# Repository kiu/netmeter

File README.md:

# netmeter
*netmeter* is a trio of analog panel meters showing the up-/download speed of my AVM FRITZ!Box 7360 and ping roundtrip times.

Video: https://youtu.be/6VHqjQCAy3I

# Inspiration
*netmeter* is inspired by the 10 year old [megabitmeter](http://dk7sl.de/2010/11/11/megabitmeter/) and its - now defunct - commercial version [megabitmeter](http://megabitmeter.de).

# Tech Details
The [ESP32-DevKitC V4](https://www.espressif.com/en/products/devkits/esp32-devkitc) offers a powerful plug and play solution providing the core functionality of *netmeter*.
It connects to the network via wifi and polls the [UPnP](https://en.wikipedia.org/wiki/Universal_Plug_and_Play) interface of the FRITZ!Box obtaining the current transmitted and received bytes count of the WAN interface. In addition it runs a simple ping command to determine the roundtrip time. The results are transformed into PWM signals driving the meters.

The mechanical design features horizontal and vertical mounting of the panel meters. The included custom scales can be omitted to save costs. In that case a standard scale - e.g. 100A = 100 MBit/s - can be used.

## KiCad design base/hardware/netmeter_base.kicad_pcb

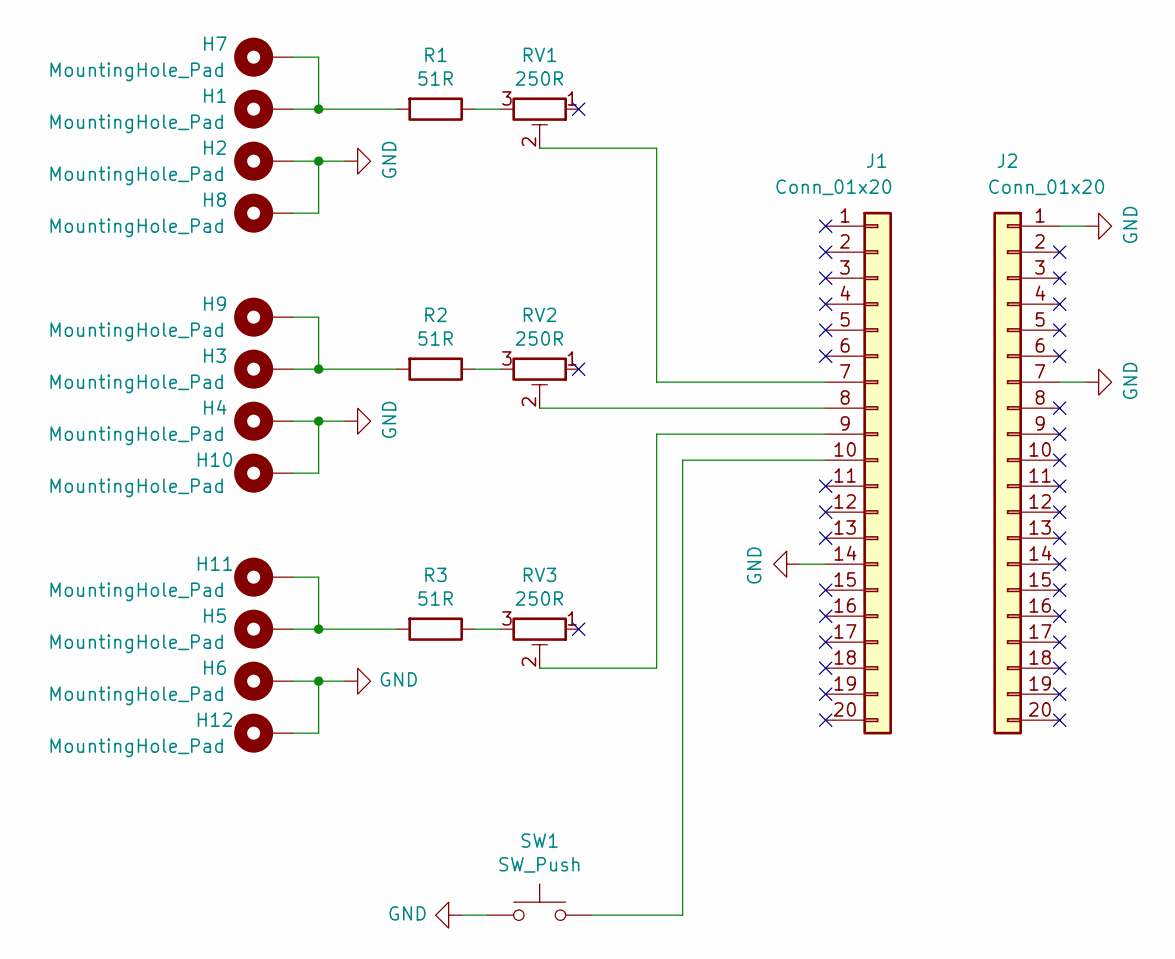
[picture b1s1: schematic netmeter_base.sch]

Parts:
H1, H2, H3, H4, H5, H6, H7, H8, H9, H10, H11, H12: MountingHole_Pad; MountingHole_4.3mm_M4_Pad_Via
J1, J2: Conn_01x20; Socket_Strip_Straight_1x20_Pitch2.54mm
R1, R2, R3: 51R; R_0805_HandSoldering
RV1, RV2, RV3: 250R; Potentiometer_Trimmer_Piher_PT-10v10_Horizontal_Px10.0mm_Py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
SW1: SW_Push; SW_SPST_B3S-1000

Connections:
GND: H2.1, H4.1, H6.1, H8.1, H10.1, H12.1, J1.14, J2.1, J2.7, SW1.2
unnamed: H1.1, H7.1, R1.2
unnamed: H3.1, H9.1, R2.2
unnamed: H5.1, H11.1, R3.2
unnamed: J1.7, RV1.2
unnamed: J1.8, RV2.2
unnamed: J1.9, RV3.2
unnamed: J1.10, SW1.1
unnamed: R1.1, RV1.3
unnamed: R2.1, RV2.3
unnamed: R3.1, RV3.3

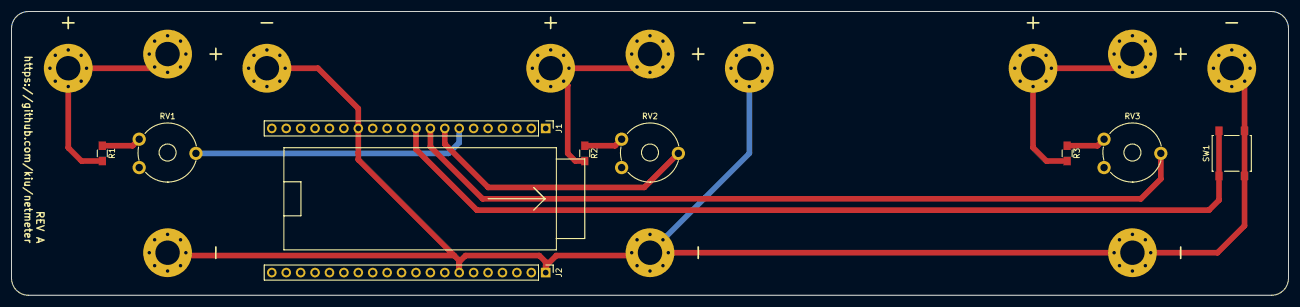
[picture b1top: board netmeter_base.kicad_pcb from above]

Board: 2 copper layers, 225.0 x 50.0 mm, 21 parts (0 on the bottom side), 11 nets.

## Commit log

2020-09-19 Initial REV A
2020-09-25 Fixed kernel crashes Switching between modes is quick now ...
2020-10-03 Added le youtube
2020-10-03 markdown is difficult
2020-10-03 Moved video
